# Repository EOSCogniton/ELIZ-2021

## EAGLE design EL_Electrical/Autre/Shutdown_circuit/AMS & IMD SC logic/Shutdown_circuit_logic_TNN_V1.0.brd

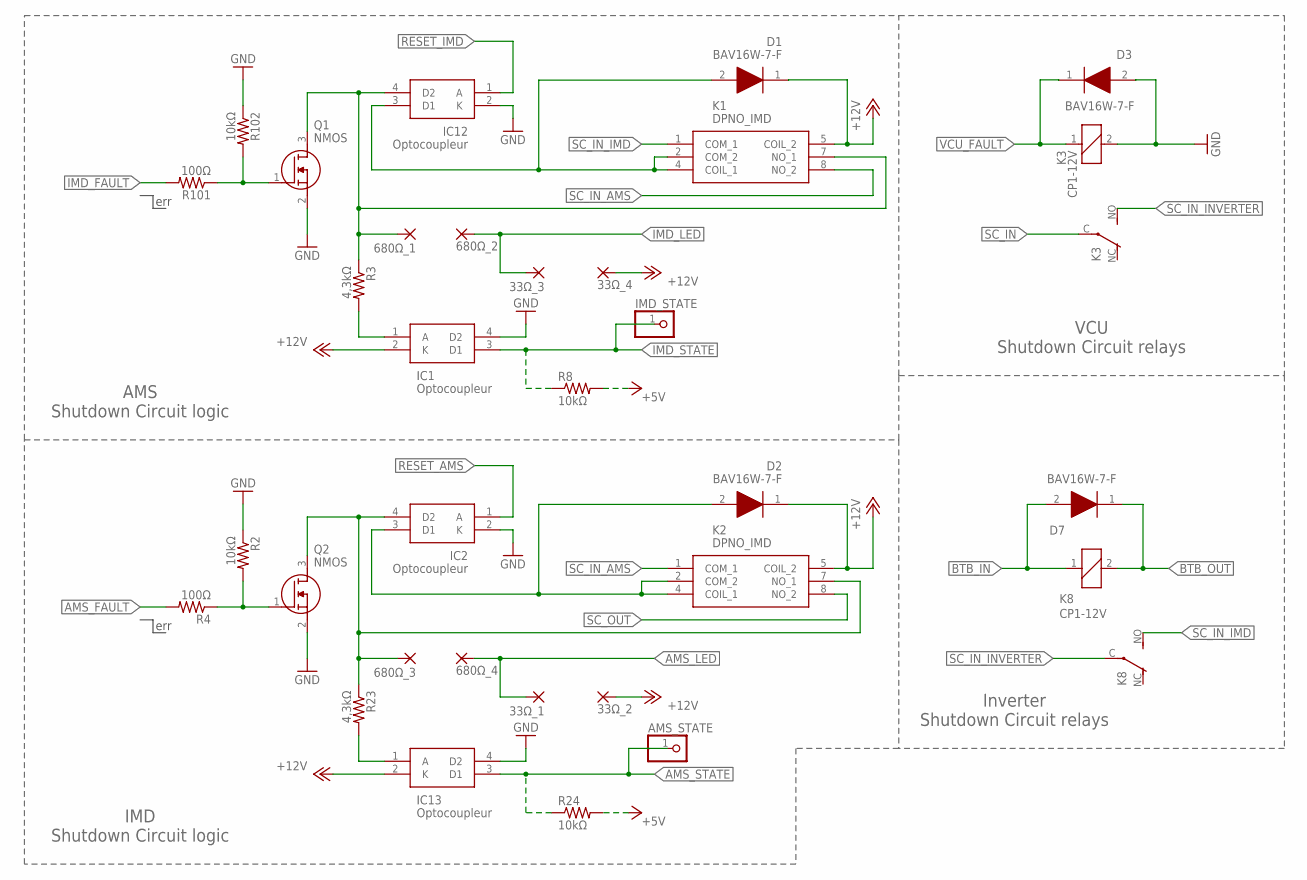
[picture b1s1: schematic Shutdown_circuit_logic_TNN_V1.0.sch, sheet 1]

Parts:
33Ω_1, 33Ω_2, 33Ω_3, 33Ω_4, 680Ω_1, 680Ω_2, 680Ω_3, 680Ω_4: 1,6/0,8
AMS_STATE: PINHD-1X1; 1X01
D1, D2, D3, D7: BAV16W-7-F; SOD3716X145N
IC1, IC2, IC12, IC13: Optocoupleur; SOP254P680X230-4N
IMD_STATE: PINHD-1X1; 1X01
K1, K2: DPNO_IMD; AHES3292
K3, K8: CP1-12V; CP1
Q1, Q2: NMOS; SOT96P240X110-3N
R2, R8, R24, R102: 10kΩ; R0603
R3, R23: 4,3kΩ; R0603
R4, R101: 100Ω; R0603

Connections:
+5V: R8.2, R24.2; also elsewhere on the board
+12V: 33Ω_2.1, 33Ω_4.1, D1.1 (K), D2.1 (K), IC1.2 (K), IC13.2 (K), K1.5 (COIL_2), K2.5 (COIL_2); also elsewhere on the board
AMS_FAULT: R4.2; also elsewhere on the board
AMS_LED: 33Ω_1.1, 680Ω_4.1; also elsewhere on the board
AMS_STATE: AMS_STATE.1, IC13.3 (D1), R24.1; also elsewhere on the board
BTB_IN: D7.2 (A), K8.1; also elsewhere on the board
BTB_OUT: D7.1 (K), K8.2; also elsewhere on the board
GND: D3.2 (A), IC1.4 (D2), IC2.2 (K), IC12.2 (K), IC13.4 (D2), K3.2, Q1.2 (S), Q2.2 (S), R2.1, R102.1; also elsewhere on the board
IMD_FAULT: R101.2; also elsewhere on the board
IMD_LED: 33Ω_3.1, 680Ω_2.1; also elsewhere on the board
IMD_STATE: IC1.3 (D1), IMD_STATE.1, R8.1; also elsewhere on the board
unnamed: Q2.1 (G), R2.2, R4.1
unnamed: Q1.1 (G), R101.1, R102.2
unnamed: 680Ω_3.1, IC2.4 (D2), K2.7 (NO_1), Q2.3 (D), R23.1
unnamed: IC1.1 (A), R3.2
unnamed: 680Ω_1.1, IC12.4 (D2), K1.7 (NO_1), Q1.3 (D), R3.1
unnamed: D2.2 (A), IC2.3 (D1), K2.2 (COM_2), K2.4 (COIL_1)
unnamed: IC13.1 (A), R23.2
unnamed: D1.2 (A), IC12.3 (D1), K1.2 (COM_2), K1.4 (COIL_1)
RESET_AMS: IC2.1 (A); also elsewhere on the board
RESET_IMD: IC12.1 (A); also elsewhere on the board
SC_IN: K3.C; also elsewhere on the board
SC_IN_AMS: K1.8 (NO_2), K2.1 (COM_1)
SC_IN_IMD: K1.1 (COM_1), K8.NO (S)
SC_IN_INVERTER: K3.NO (S), K8.C
SC_OUT: K2.8 (NO_2); also elsewhere on the board
VCU_FAULT: D3.1 (K), K3.1; also elsewhere on the board

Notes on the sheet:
err
AMS Shutdown Circuit logic
IMD Shutdown Circuit logic
VCU Shutdown Circuit relays
Inverter Shutdown Circuit relays

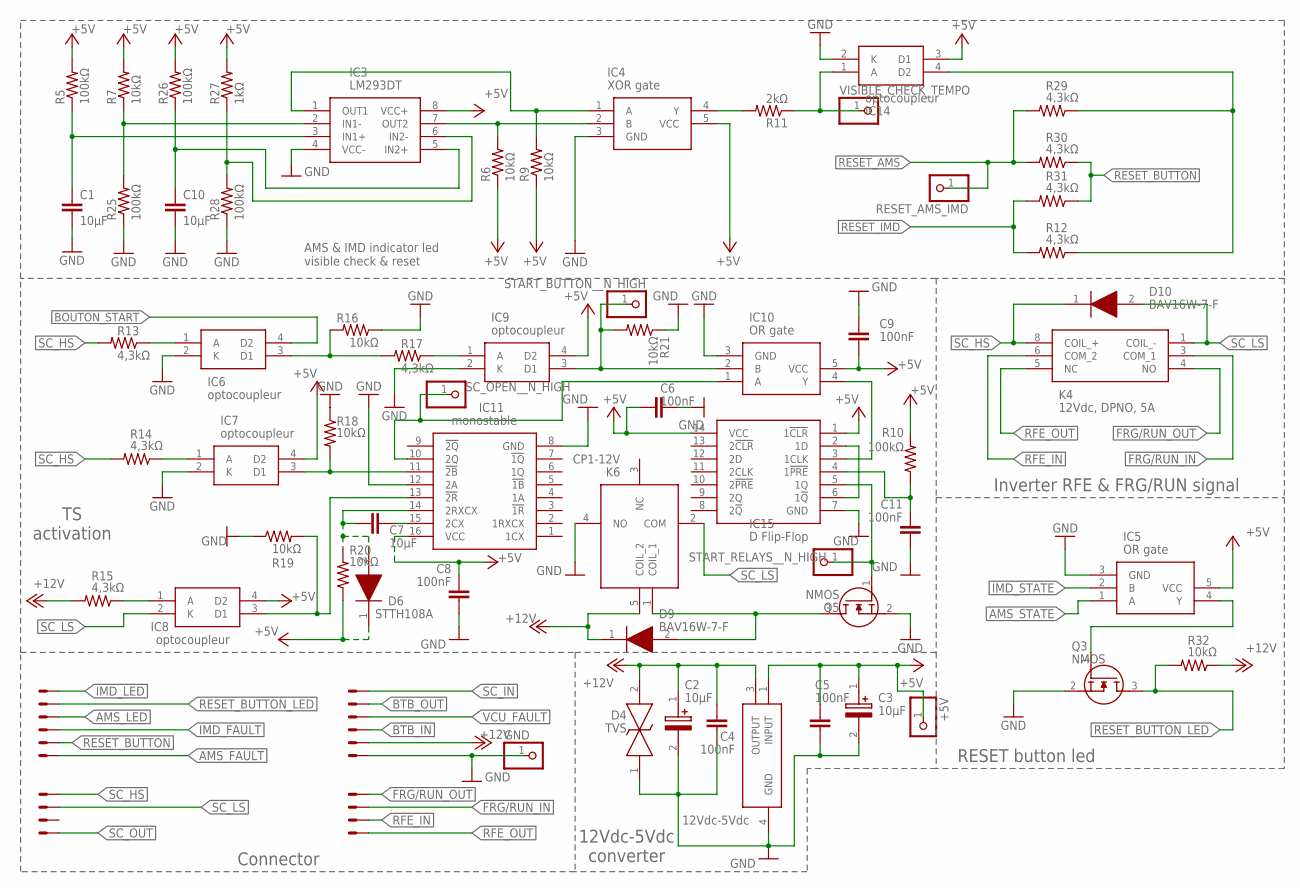
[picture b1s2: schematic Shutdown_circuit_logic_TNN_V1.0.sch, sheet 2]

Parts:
+5V: PINHD-1X1; 1X01
C1, C7, C10: 10μF; C0603
C2, C3: 10μF; CAPPRD200W55D525H1200
C4, C5, C6, C8, C9, C11: 100nF; C0603
CONVERTER: 12Vdc-5Vdc; TO228P972X240-3N
D4: TVS; SOD-323
D6: STTH108A; DIOM5126X265N
D9, D10: BAV16W-7-F; SOD3716X145N
GND: PINHD-1X1; 1X01
IC3: LM293DT; SOIC127P600X175-8N
IC4: XOR gate; SOT65P210X110-5N
IC5, IC10: OR gate; SOT95P280X145-5N
IC6, IC7, IC8, IC9, IC14: optocoupleur; SOP254P680X230-4N
IC11: monostable; SOIC127P600X175-16N
IC15: D Flip-Flop; SOIC127P600X175-14N
K4: 12Vdc, DPNO, 5A; G6B2214PUS12DC
K6: CP1-12V; CP1FORMC_1
Q3, Q5: NMOS; SOT96P240X110-3N
R5, R10, R25, R26, R28: 100kΩ; R0603
R6, R7, R9, R16, R18, R19, R20, R21, R32: 10kΩ; R0603
R11: 2kΩ; R0603
R12, R13, R14, R15, R17, R29, R30, R31: 4,3kΩ; R0603
R27: 1kΩ; R0603
RESET_AMS_IMD: PINHD-1X1; 1X01
SC_OPEN__N_HIGH: PINHD-1X1; 1X01
START_BUTTON__N_HIGH: PINHD-1X1; 1X01
START_RELAYS__N_HIGH: PINHD-1X1; 1X01
VISIBLE_CHECK_TEMPO: PINHD-1X1; 1X01
X1, X2: 22-23-2041
X3, X4: 22-23-2061

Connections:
+5V: +5V.1, C3.1 (+), C5.1, C6.2, C8.2, C9.2, CONVERTER.1 (INPUT), D6.1 (K), IC3.8 (VCC+), IC4.5 (VCC), IC5.5 (VCC), IC7.4 (D2), IC8.4 (D2), IC9.4 (D2), IC10.5 (VCC), IC11.16 (VCC), IC14.3 (D1), IC15.1 (1!CLR), IC15.14 (VCC), R5.2, R6.1, R7.2, R9.1, R10.2, R20.1, R26.2, R27.2; also elsewhere on the board
+12V: C2.1 (+), C4.1, CONVERTER.3 (OUTPUT), D4.2, D9.1 (K), K6.5 (COIL_2), R15.2, R32.1, X4.2; also elsewhere on the board
AMS_FAULT: X3.1; also elsewhere on the board
AMS_LED: X3.4; also elsewhere on the board
AMS_STATE: IC5.1 (A); also elsewhere on the board
BOUTON_START: IC6.4 (D2)
BTB_IN: X4.3; also elsewhere on the board
BTB_OUT: X4.5; also elsewhere on the board
FRG/RUN_IN: K4.3 (COM_1), X2.3
FRG/RUN_OUT: K4.4 (NO), X2.4
GND: C1.2, C2.2 (-), C3.2 (-), C4.2, C5.2, C6.1, C8.1, C9.1, C10.2, C11.1, CONVERTER.4 (GND), D4.1, GND.1, IC3.4 (VCC-), IC4.3 (GND), IC5.3 (GND), IC6.2 (K), IC7.2 (K), IC9.2 (K), IC10.3 (GND), IC11.8 (GND), IC11.12 (2A), IC14.2 (K), IC15.7 (GND), K6.4 (NO), Q3.2 (S), Q5.2 (S), R16.1, R18.1, R19.1, R21.1, R25.1, R28.1, X4.1; also elsewhere on the board
IMD_FAULT: X3.3; also elsewhere on the board
IMD_LED: X3.6; also elsewhere on the board
IMD_STATE: IC5.2 (B); also elsewhere on the board
unnamed: C1.1, IC3.3 (IN1+), R5.1
unnamed: IC3.2 (IN1-), R7.1, R25.2
unnamed: IC6.1 (A), R13.1
unnamed: C10.1, IC3.5 (IN2+), R26.1
unnamed: IC6.3 (D1), R16.2, R17.2
unnamed: IC10.1 (A), IC11.10 (2Q), SC_OPEN__N_HIGH.1
unnamed: C7.2, D6.2 (A), IC11.14 (2RXCX), R20.2
unnamed: IC7.1 (A), R14.1
unnamed: IC7.3 (D1), IC11.11 (!2B), R18.2
unnamed: IC8.1 (A), R15.1
unnamed: IC8.3 (D1), IC11.13 (!2R), R19.2
unnamed: IC9.1 (A), R17.1
unnamed: IC9.3 (D1), IC10.2 (B), R21.2, START_BUTTON__N_HIGH.1
unnamed: IC15.5 (1Q), Q5.1 (G), START_RELAYS__N_HIGH.1
unnamed: IC5.4 (Y), Q3.1 (G)
unnamed: IC10.4 (Y), IC15.3 (1CLK)
unnamed: IC3.6 (IN2-), R27.1, R28.2
unnamed: IC3.1 (OUT1), IC4.1 (A), R9.2
unnamed: IC3.7 (OUT2), IC4.2 (B), R6.2
unnamed: IC14.1 (A), R11.1, VISIBLE_CHECK_TEMPO.1
unnamed: IC14.4 (D2), R12.1, R29.1
unnamed: IC4.4 (Y), R11.2
unnamed: C7.1, IC11.15 (2CX)
unnamed: IC15.2 (1D), IC15.6 (1!Q)
unnamed: D9.2 (A), K6.1 (COIL_1), Q5.3 (D)
unnamed: C11.2, IC15.4 (1!PRE), R10.1
RESET_AMS: R29.2, R30.2, RESET_AMS_IMD.1; also elsewhere on the board
RESET_BUTTON: R30.1, R31.1, X3.2
RESET_BUTTON_LED: Q3.3 (D), R32.2, X3.5
RESET_IMD: R12.2, R31.2; also elsewhere on the board
RFE_IN: K4.6 (COM_2), X2.2
RFE_OUT: K4.5 (NC), X2.1
SC_HS: D10.1 (K), K4.8 (COIL_+), R13.2, R14.2, X1.4
SC_IN: X4.6; also elsewhere on the board
SC_LS: D10.2 (A), IC8.2 (K), K4.1 (COIL_-), K6.2 (COM), X1.3
SC_OUT: X1.1; also elsewhere on the board
VCU_FAULT: X4.4; also elsewhere on the board

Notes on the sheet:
AMS & IMD indicator led visible check & reset
TS activation
Connector
12Vdc-5Vdc converter
Inverter RFE & FRG/RUN signal
RESET button led

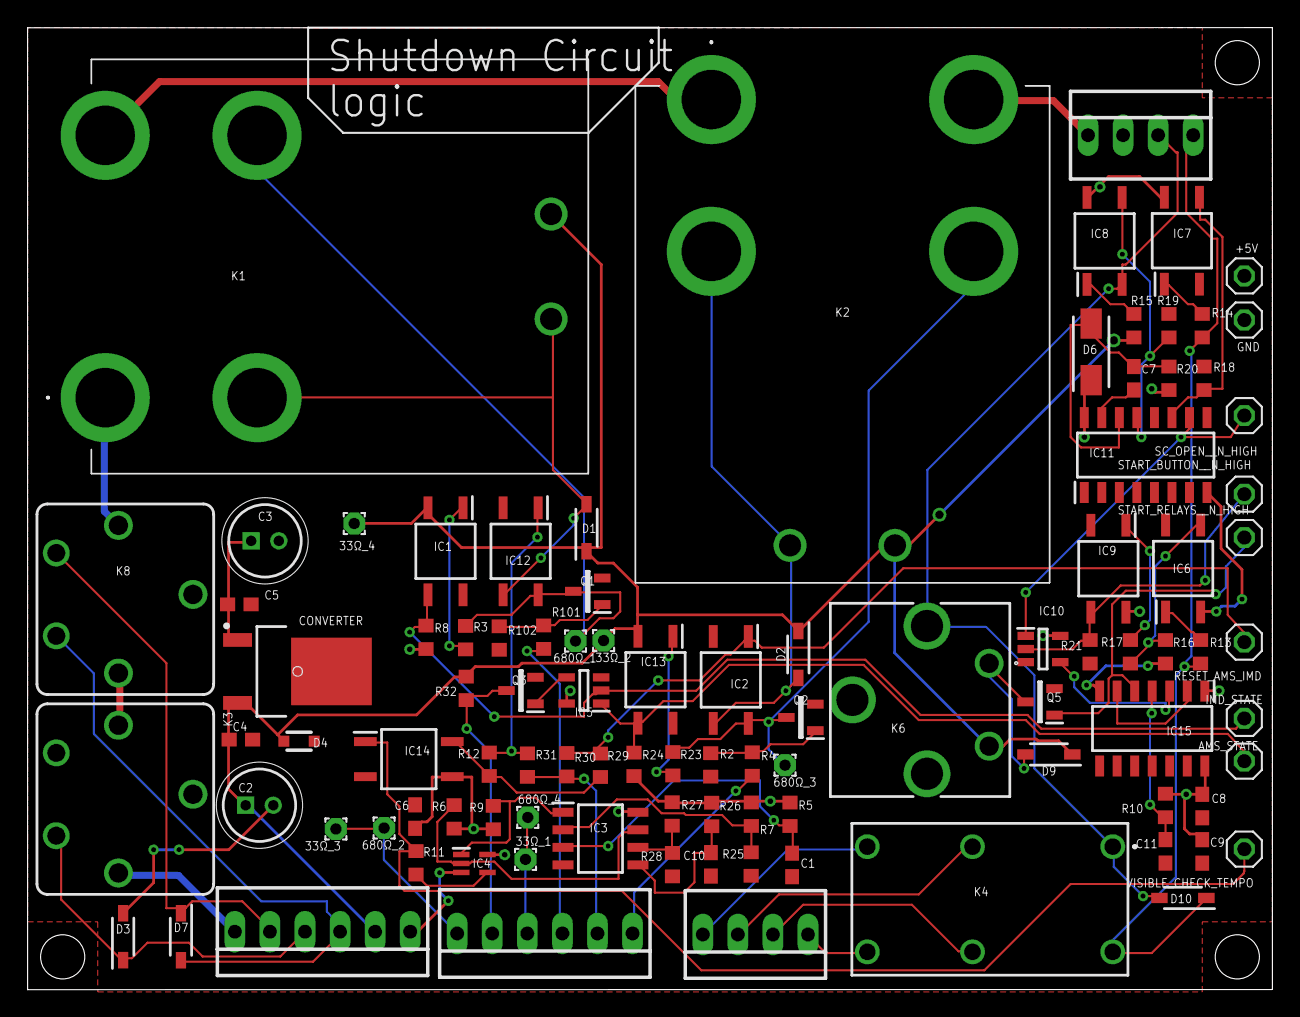
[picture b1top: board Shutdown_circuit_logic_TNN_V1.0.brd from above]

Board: 2 copper layers, 90.2 x 69.7 mm, 98 parts (0 on the bottom side), 61 nets.

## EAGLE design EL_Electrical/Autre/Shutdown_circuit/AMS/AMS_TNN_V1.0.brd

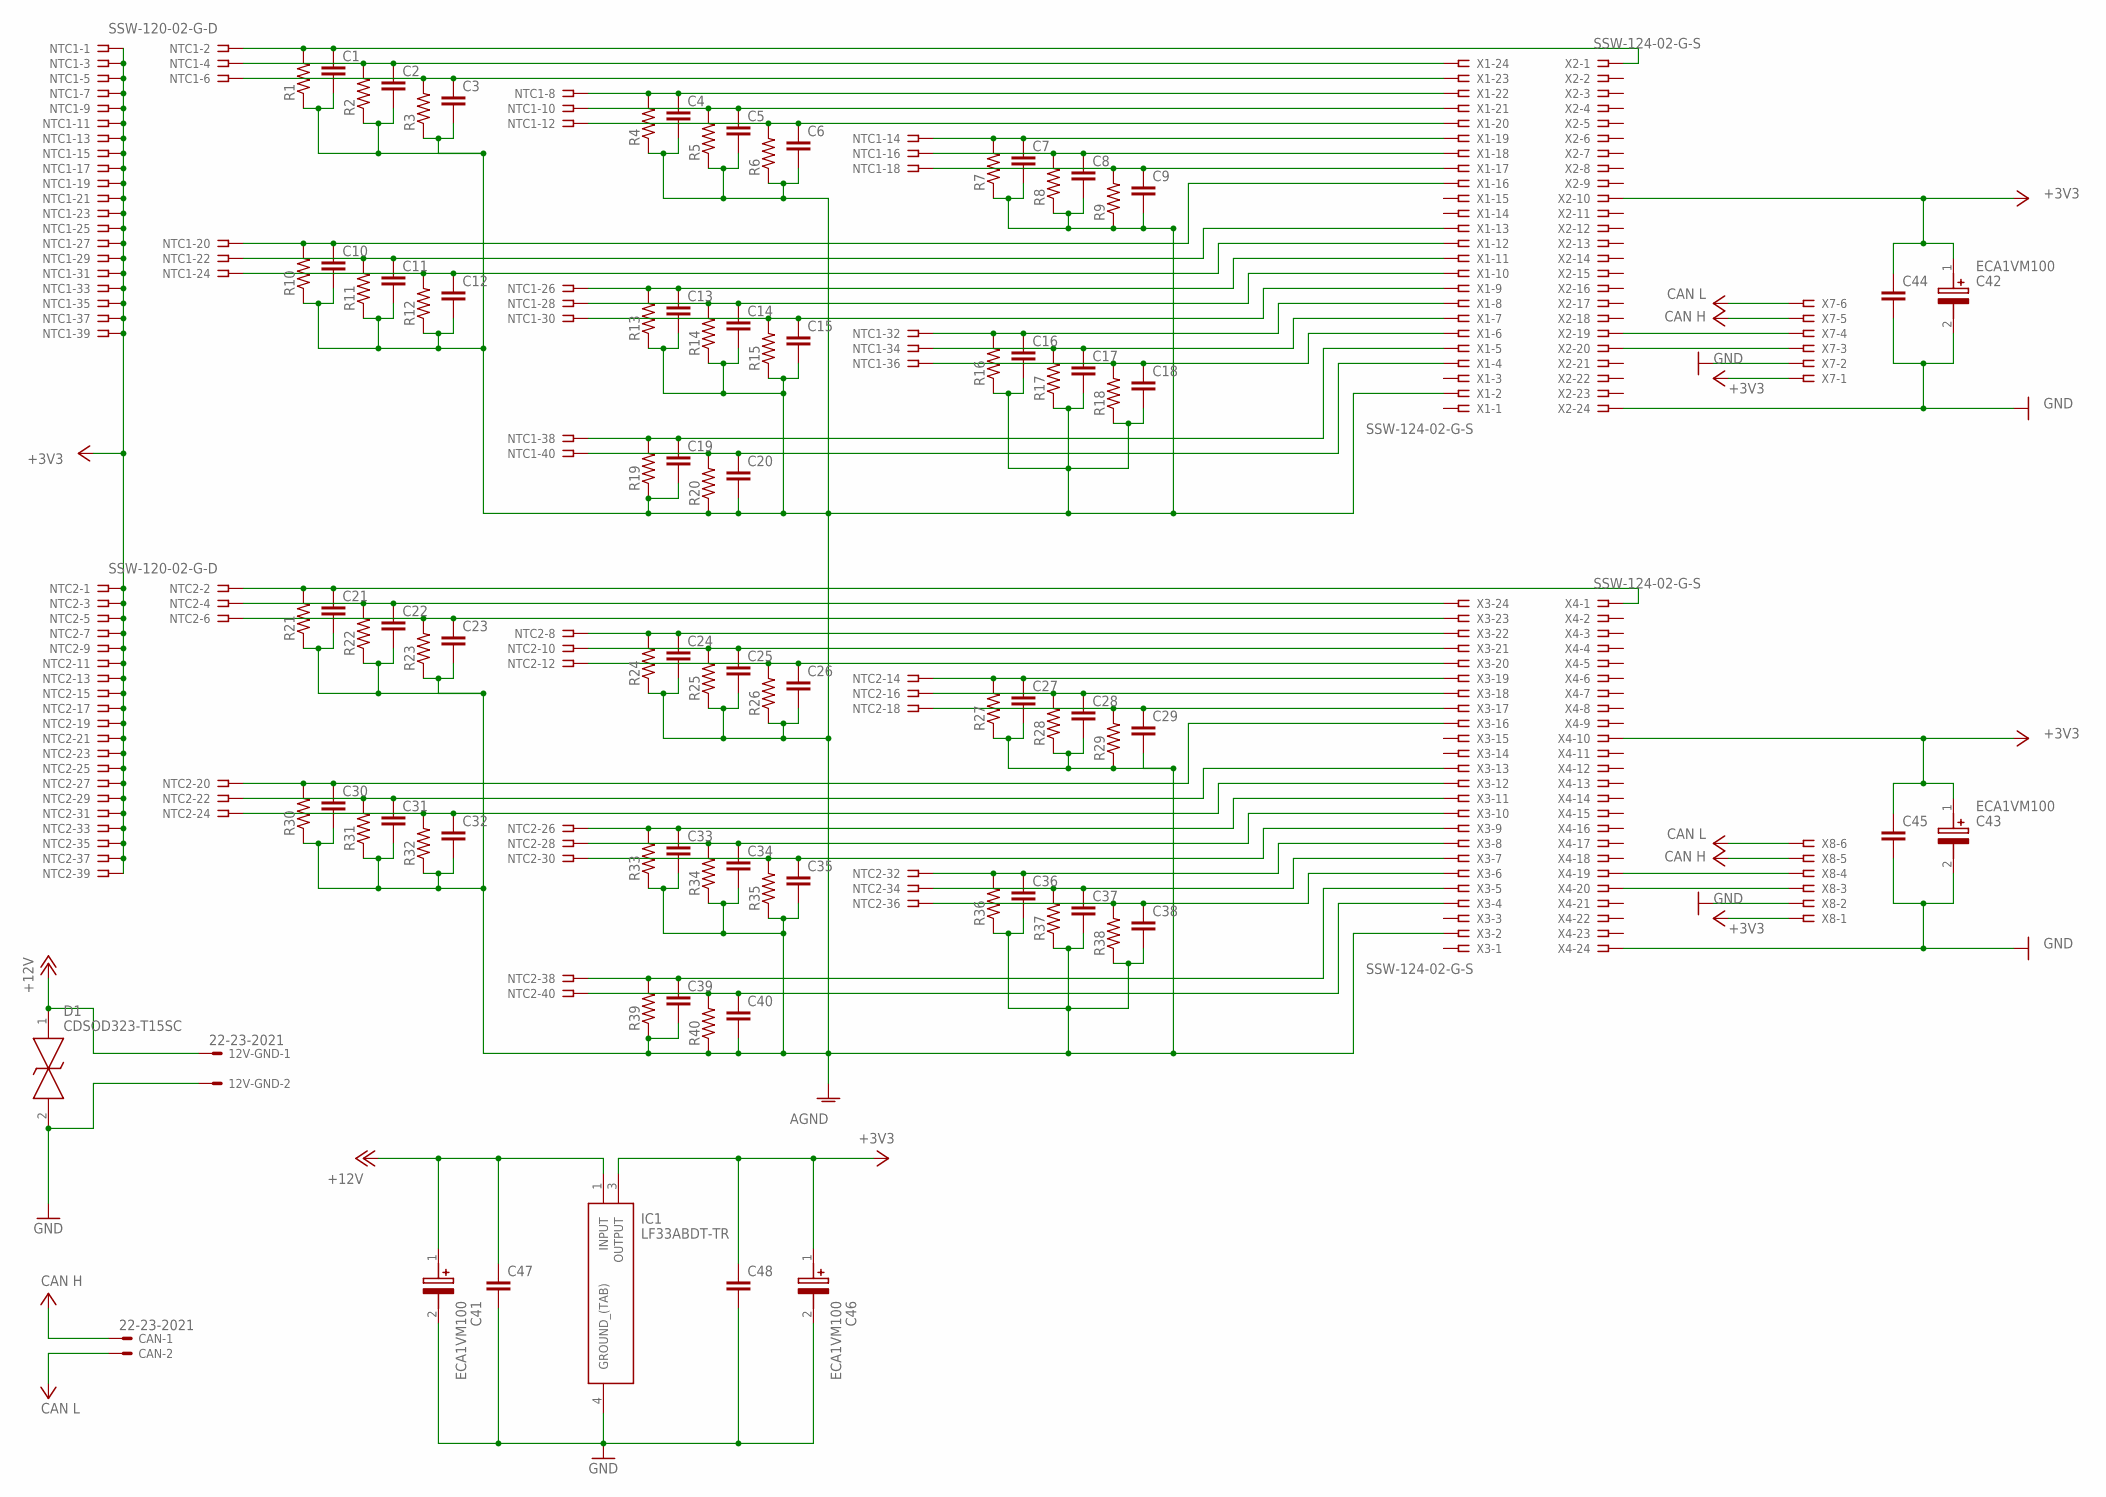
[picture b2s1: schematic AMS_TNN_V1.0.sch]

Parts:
12V-GND: 22-23-2021
C1, C2, C3, C4, C5, C6, C7, C8, C9, C10, C11, C12, C13, C14, C15, C16, C17, C18, C19, C20, C21, C22, C23, C24, C25, C26, C27, C28, C29, C30, C31, C32, C33, C34, C35, C36, C37, C38, C39, C40, C44, C45, C47, C48: C-EUC0603; C0603
C41, C42, C43, C46: ECA1VM100; CAPPRD200W55D525H1200
CAN: 22-23-2021
D1: CDSOD323-T15SC; SOD-323
IC1: LF33ABDT-TR; TO228P972X240-3N
NTC1, NTC2: SSW-120-02-G-D
R1, R2, R3, R4, R5, R6, R7, R8, R9, R10, R11, R12, R13, R14, R15, R16, R17, R18, R19, R20, R21, R22, R23, R24, R25, R26, R27, R28, R29, R30, R31, R32, R33, R34, R35, R36, R37, R38, R39, R40: R-US_R0603; R0603
X1, X2, X3, X4: SSW-124-02-G-S
X7, X8: SSW-106-02-G-S

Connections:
+3V3: C42.1 (+), C43.1 (+), C44.1, C45.1, C46.1 (+), C48.1, IC1.3 (OUTPUT), NTC1.1, NTC1.3, NTC1.5, NTC1.7, NTC1.9, NTC1.11, NTC1.13, NTC1.15, NTC1.17, NTC1.19, NTC1.21, NTC1.23, NTC1.25, NTC1.27, NTC1.29, NTC1.31, NTC1.33, NTC1.35, NTC1.37, NTC1.39, NTC2.1, NTC2.3, NTC2.5, NTC2.7, NTC2.9, NTC2.11, NTC2.13, NTC2.15, NTC2.17, NTC2.19, NTC2.21, NTC2.23, NTC2.25, NTC2.27, NTC2.29, NTC2.31, NTC2.33, NTC2.35, NTC2.37, NTC2.39, X2.10, X4.10, X7.1, X8.1
+12V: 12V-GND.1, C41.1 (+), C47.1, D1.1, IC1.1 (INPUT)
AGND: C1.2, C2.2, C3.2, C4.2, C5.2, C6.2, C7.2, C8.2, C9.2, C10.2, C11.2, C12.2, C13.2, C14.2, C15.2, C16.2, C17.2, C18.2, C19.2, C20.2, C21.2, C22.2, C23.2, C24.2, C25.2, C26.2, C27.2, C28.2, C29.2, C30.2, C31.2, C32.2, C33.2, C34.2, C35.2, C36.2, C37.2, C38.2, C39.2, C40.2, R1.1, R2.1, R3.1, R4.1, R5.1, R6.1, R7.1, R8.1, R9.1, R10.1, R11.1, R12.1, R13.1, R14.1, R15.1, R16.1, R17.1, R18.1, R19.1, R20.1, R21.1, R22.1, R23.1, R24.1, R25.1, R26.1, R27.1, R28.1, R29.1, R30.1, R31.1, R32.1, R33.1, R34.1, R35.1, R36.1, R37.1, R38.1, R39.1, R40.1, X1.2, X3.2
GND: 12V-GND.2, C41.2 (-), C42.2 (-), C43.2 (-), C44.2, C45.2, C46.2 (-), C47.2, C48.2, D1.2, IC1.4 (GROUND_(TAB)), X2.24, X4.24, X7.2, X8.2
unnamed: C1.1, NTC1.2, R1.2, X2.1
unnamed: C2.1, NTC1.4, R2.2, X1.24
unnamed: C3.1, NTC1.6, R3.2, X1.23
unnamed: C4.1, NTC1.8, R4.2, X1.22
unnamed: C5.1, NTC1.10, R5.2, X1.21
unnamed: C6.1, NTC1.12, R6.2, X1.20
unnamed: C7.1, NTC1.14, R7.2, X1.19
unnamed: C8.1, NTC1.16, R8.2, X1.18
unnamed: C9.1, NTC1.18, R9.2, X1.17
unnamed: C10.1, NTC1.20, R10.2, X1.16
unnamed: C11.1, NTC1.22, R11.2, X1.13
unnamed: C12.1, NTC1.24, R12.2, X1.12
unnamed: C13.1, NTC1.26, R13.2, X1.11
unnamed: C14.1, NTC1.28, R14.2, X1.10
unnamed: C15.1, NTC1.30, R15.2, X1.9
unnamed: C18.1, NTC1.36, R18.2, X1.6
unnamed: C16.1, NTC1.32, R16.2, X1.8
unnamed: C17.1, NTC1.34, R17.2, X1.7
unnamed: C21.1, NTC2.2, R21.2, X4.1
unnamed: C20.1, NTC1.40, R20.2, X1.4
unnamed: C22.1, NTC2.4, R22.2, X3.24
unnamed: C23.1, NTC2.6, R23.2, X3.23
unnamed: C24.1, NTC2.8, R24.2, X3.22
unnamed: C25.1, NTC2.10, R25.2, X3.21
unnamed: C26.1, NTC2.12, R26.2, X3.20
unnamed: C27.1, NTC2.14, R27.2, X3.19
unnamed: C28.1, NTC2.16, R28.2, X3.18
unnamed: C29.1, NTC2.18, R29.2, X3.17
unnamed: C30.1, NTC2.20, R30.2, X3.16
unnamed: C31.1, NTC2.22, R31.2, X3.13
unnamed: C32.1, NTC2.24, R32.2, X3.12
unnamed: C33.1, NTC2.26, R33.2, X3.11
unnamed: C34.1, NTC2.28, R34.2, X3.10
unnamed: C35.1, NTC2.30, R35.2, X3.9
unnamed: C36.1, NTC2.32, R36.2, X3.8
unnamed: C37.1, NTC2.34, R37.2, X3.7
unnamed: C38.1, NTC2.36, R38.2, X3.6
unnamed: C40.1, NTC2.40, R40.2, X3.4
unnamed: C39.1, NTC2.38, R39.2, X3.5
unnamed: X2.20, X7.3
unnamed: X2.19, X7.4
unnamed: X4.20, X8.3
unnamed: X4.19, X8.4
unnamed: C19.1, NTC1.38, R19.2, X1.5
V+: CAN.1, X7.5, X8.5
V-: CAN.2, X7.6, X8.6

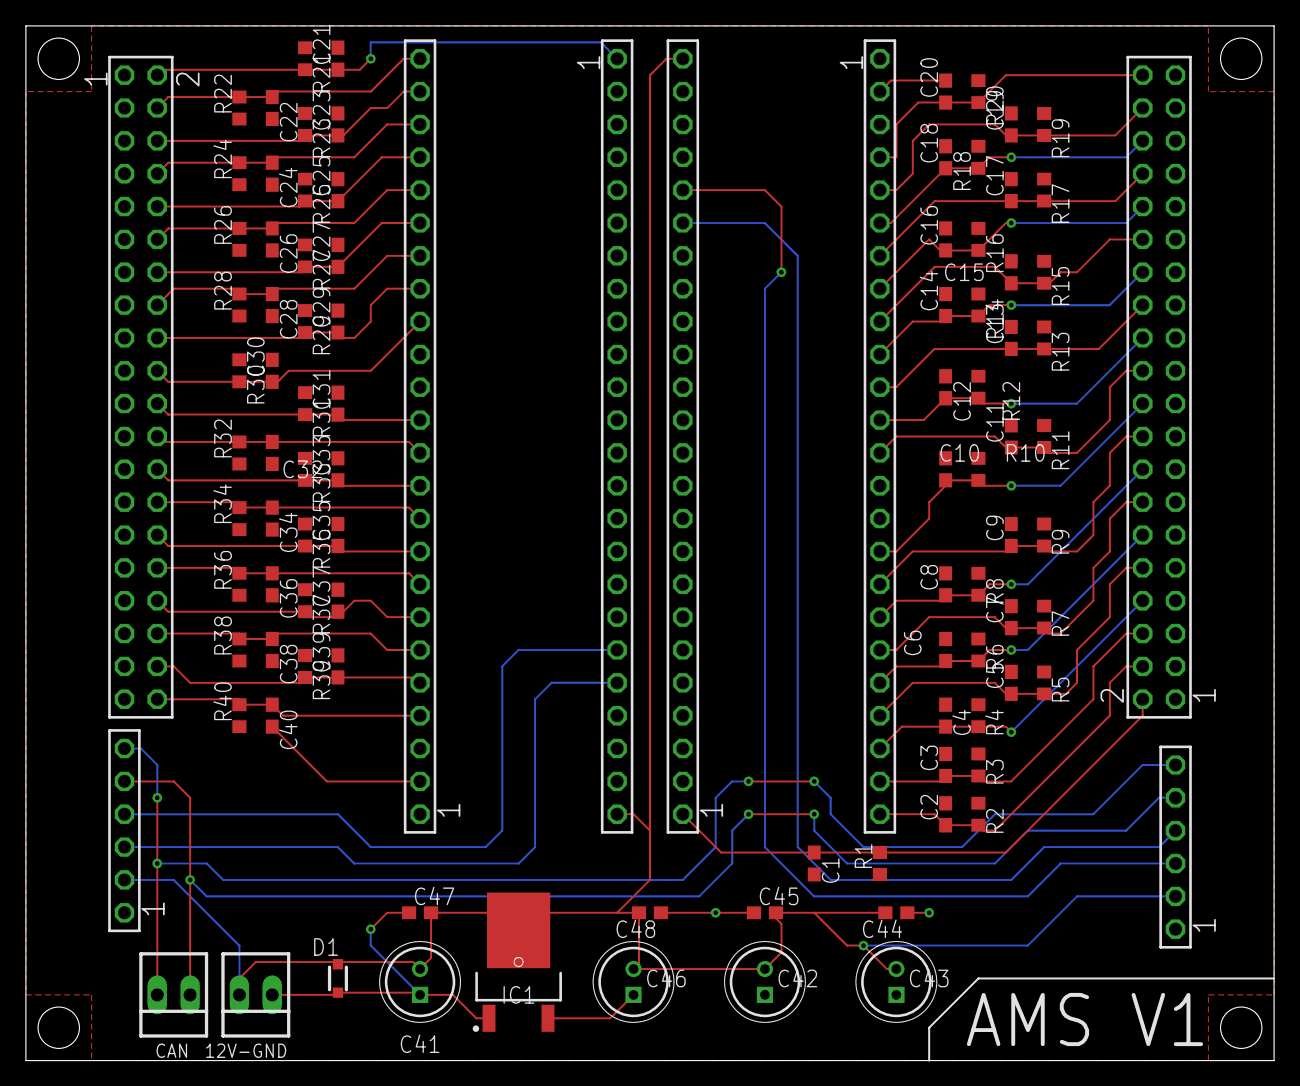
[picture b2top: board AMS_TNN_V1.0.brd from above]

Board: 2 copper layers, 96.5 x 80.0 mm, 100 parts (0 on the bottom side), 50 nets.

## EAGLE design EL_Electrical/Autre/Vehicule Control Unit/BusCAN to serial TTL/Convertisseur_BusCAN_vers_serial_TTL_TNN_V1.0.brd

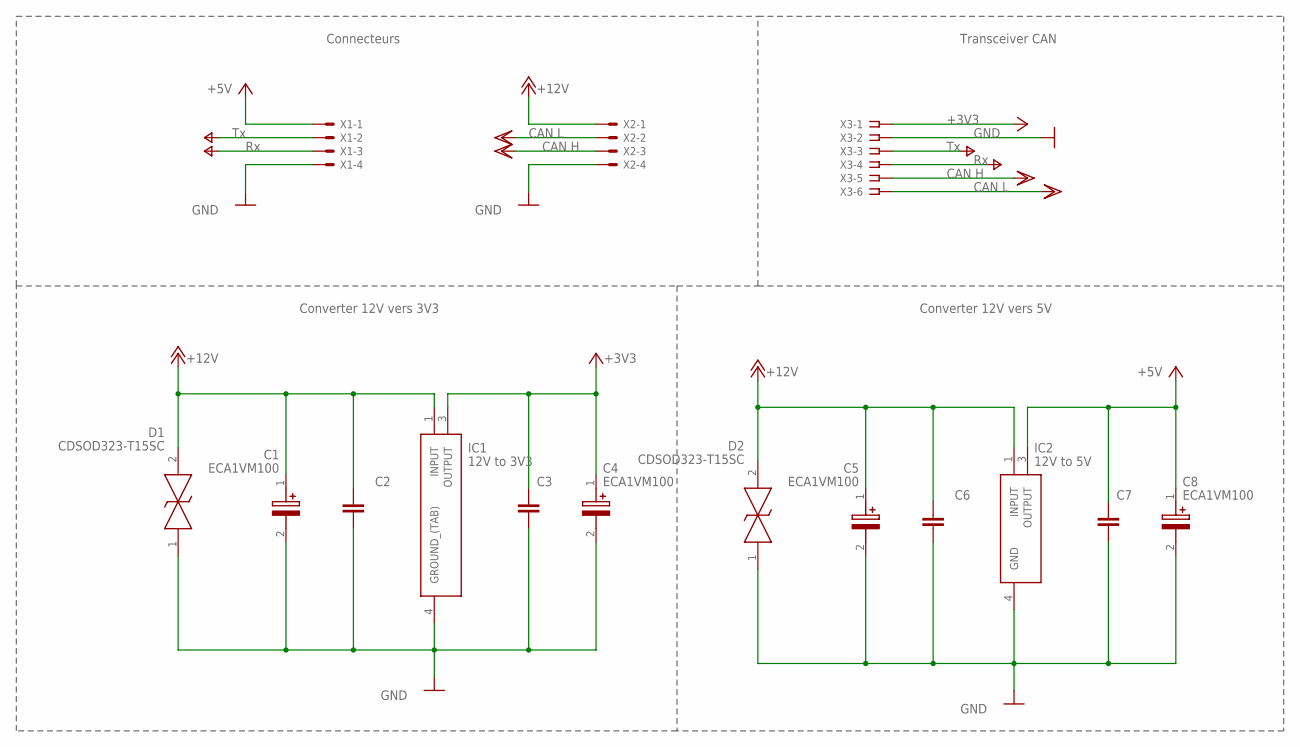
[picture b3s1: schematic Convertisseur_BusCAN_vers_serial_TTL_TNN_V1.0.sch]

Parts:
C1, C4, C5, C8: ECA1VM100; CAPPRD200W55D525H1200
C2, C3, C6, C7: C-EUC0603; C0603
D1, D2: CDSOD323-T15SC; SOD-323
IC1: 12V to 3V3; TO228P972X240-3N
IC2: 12V to 5V; TO228P972X240-3N
X1, X2: KK-156-4
X3: SSW-106-02-G-S

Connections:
+3V3: C3.1, C4.1 (+), IC1.3 (OUTPUT), X3.1
+5V: C7.1, C8.1 (+), IC2.3 (OUTPUT), X1.1
+12V: C1.1 (+), C2.1, C5.1 (+), C6.1, D1.2, D2.2, IC1.1 (INPUT), IC2.1 (INPUT), X2.1
CANH: X2.3, X3.5
CANL: X2.2, X3.6
GND: C1.2 (-), C2.2, C3.2, C4.2 (-), C5.2 (-), C6.2, C7.2, C8.2 (-), D1.1, D2.1, IC1.4 (GROUND_(TAB)), IC2.4 (GND), X1.4, X2.4, X3.2
RX: X1.3, X3.4
TX: X1.2, X3.3

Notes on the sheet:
Converter 12V vers 3V3
Converter 12V vers 5V
Transceiver CAN
Connecteurs

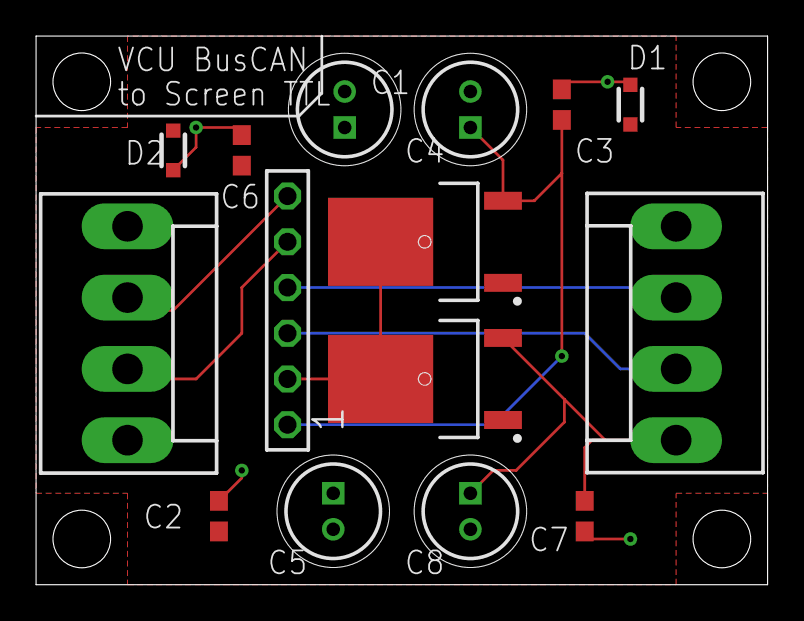
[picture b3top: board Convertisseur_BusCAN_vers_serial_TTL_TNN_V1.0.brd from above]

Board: 2 copper layers, 40.6 x 30.5 mm, 15 parts (0 on the bottom side), 8 nets.
